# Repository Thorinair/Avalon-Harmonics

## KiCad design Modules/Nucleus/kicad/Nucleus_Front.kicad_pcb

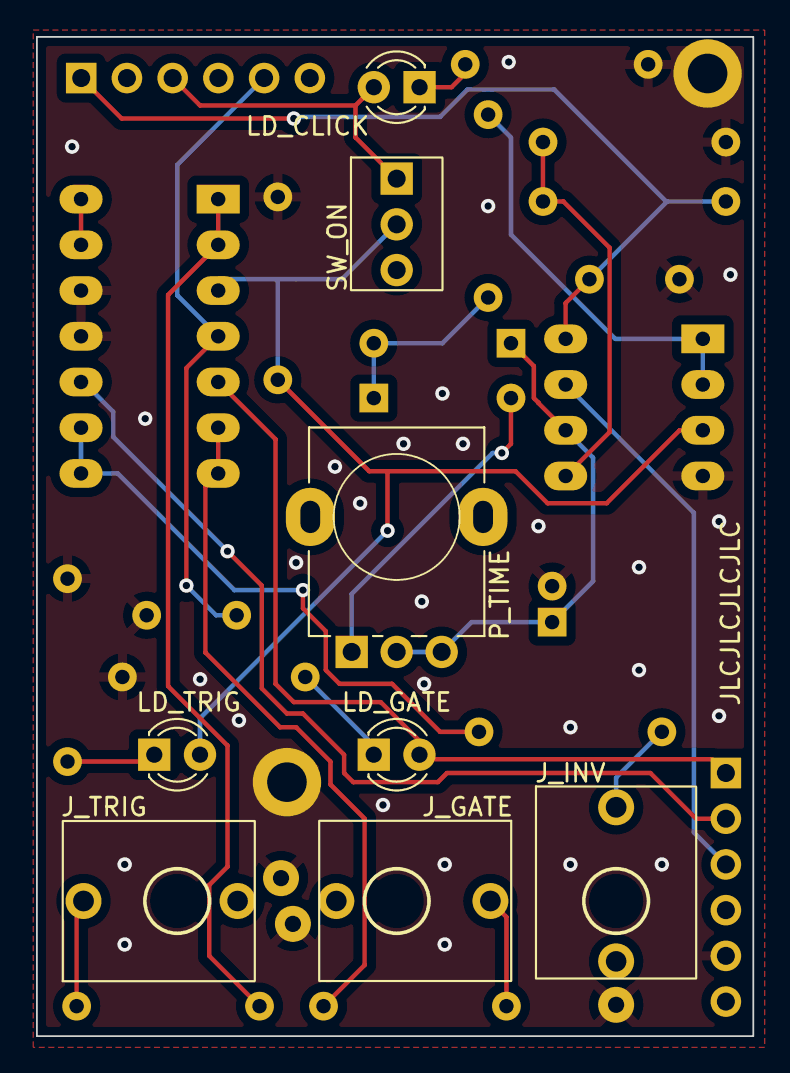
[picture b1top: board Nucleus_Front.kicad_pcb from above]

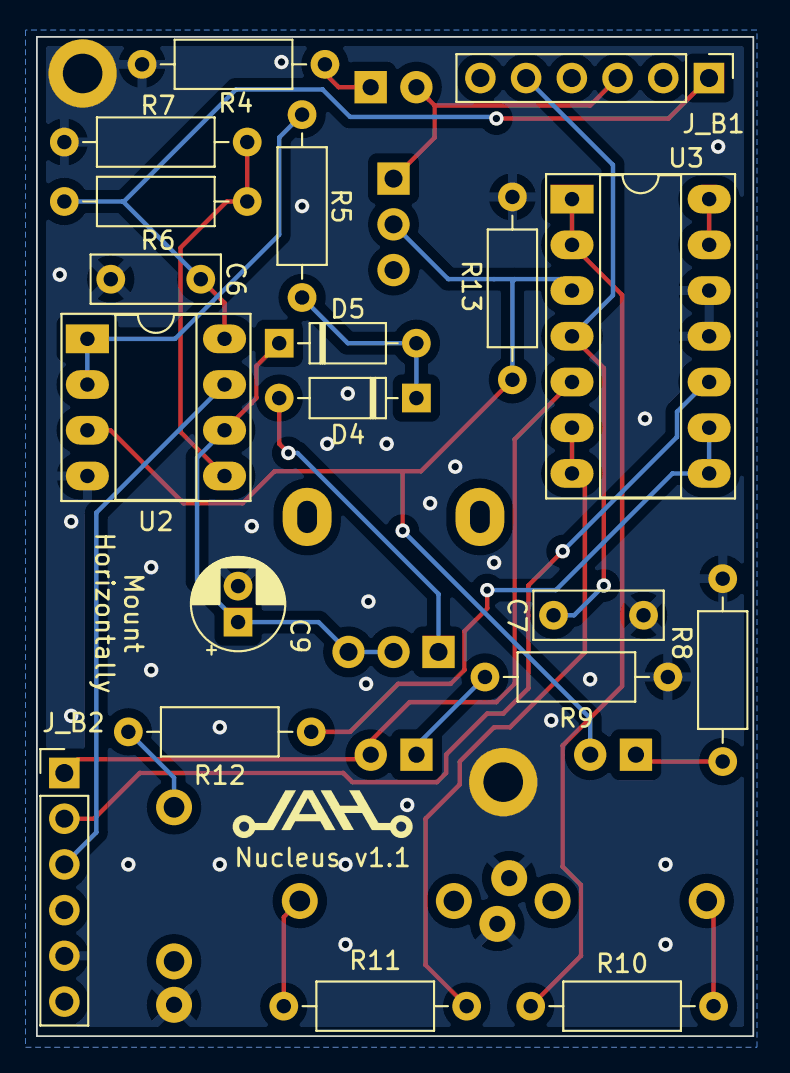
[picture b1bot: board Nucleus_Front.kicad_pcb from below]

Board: 2 copper layers, 39.8 x 55.5 mm, 27 parts (19 on the bottom side), 23 nets.

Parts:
C6, C7: 0.1uF; C_Disc_D7.0mm_W2.5mm_P5.00mm
C9: 10uF; CP_Radial_D5.0mm_P2.00mm
D4, D5: 1N4148; D_DO-35_SOD27_P7.62mm_Horizontal
J_B1, J_B2: Conn_01x06_Female; PinHeader_1x06_P2.54mm_Vertical
J_GATE1: PJ301M-12; PJ301M-12 Offset
J_INV1: PJ301M-12
J_TRIG1: PJ301M-12; PJ301M-12 Offset
LD_CLICK1: LED; LED_D3.0mm_FlatTop
LD_GATE1: LED; LED_D3.0mm_FlatTop
LD_TRIG1: LED; LED_D3.0mm_FlatTop
P_TIME1: B100k; Potentiometer Alpha RD901F-40-00D
R4, R7, R8, R9: 10k; R_Axial_DIN0207_L6.3mm_D2.5mm_P10.16mm_Horizontal
R5: 220; R_Axial_DIN0207_L6.3mm_D2.5mm_P10.16mm_Horizontal
R6: 120k; R_Axial_DIN0207_L6.3mm_D2.5mm_P10.16mm_Horizontal
R10, R11, R12: 1k; R_Axial_DIN0207_L6.3mm_D2.5mm_P10.16mm_Horizontal
R13: 1M; R_Axial_DIN0207_L6.3mm_D2.5mm_P10.16mm_Horizontal
SW_ON1: SW_SPDT; SPDT
U2: LM358; DIP-8_W7.62mm_Socket_LongPads
U3: LM324; DIP-14_W7.62mm_Socket_LongPads

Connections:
+5V: C6.1, J_B1.1, R6.1, U2.8 (V+)
+12V: C7.1, J_B1.5, U3.4 (V+)
/GATE: J_B2.1, LD_GATE1.2 (A), U3.5 (+)
/INV: J_B2.2, U3.10 (+)
/TRIG: LD_TRIG1.2 (A), R13.1, SW_ON1.2 (B), U2.3 (+), U3.3 (+)
GND: C6.2, C7.2, C9.2, J_B2.5, J_GATE1.GND, J_INV1.GND, J_TRIG1.GND, R4.2, R7.2, R8.2, R9.2, R13.2, U2.4 (V-), U3.11 (V-), U3.12 (+)
unnamed: C9.1, D5.1 (K), P_TIME1.2, P_TIME1.3, U2.6 (-)
unnamed: D4.1 (K), D5.2 (A), R5.2
unnamed: D4.2 (A), P_TIME1.1
unnamed: J_B1.3, LD_CLICK1.2 (A), SW_ON1.1 (A)
unnamed: J_B2.3, U2.7
unnamed: J_GATE1.SIG, R11.2
unnamed: J_INV1.SIG, R12.2
unnamed: J_TRIG1.SIG, R10.2
unnamed: LD_CLICK1.1 (K), R4.1
unnamed: LD_GATE1.1 (K), R9.1
unnamed: LD_TRIG1.1 (K), R8.1
unnamed: R5.1, U2.1, U2.2 (-)
unnamed: R6.2, R7.1, U2.5 (+)
unnamed: R10.1, U3.1, U3.2 (-)
unnamed: R11.1, U3.6 (-), U3.7
unnamed: R12.1, U3.8, U3.9 (-)
unnamed: U3.13 (-), U3.14

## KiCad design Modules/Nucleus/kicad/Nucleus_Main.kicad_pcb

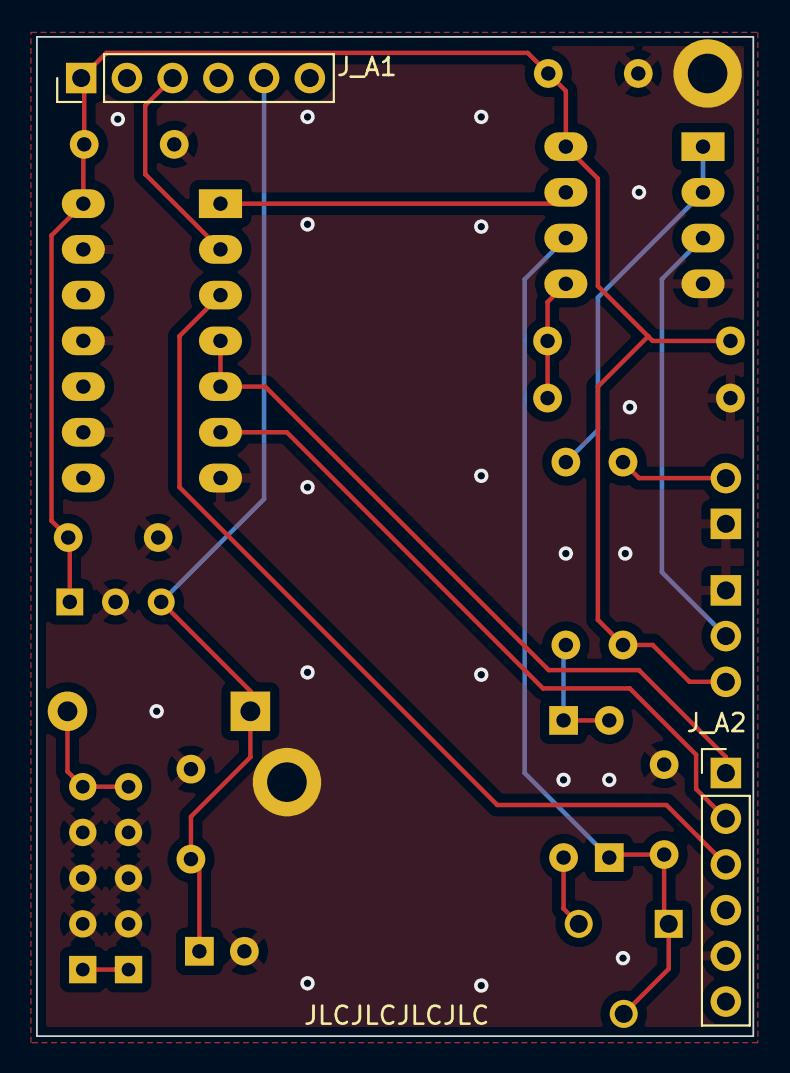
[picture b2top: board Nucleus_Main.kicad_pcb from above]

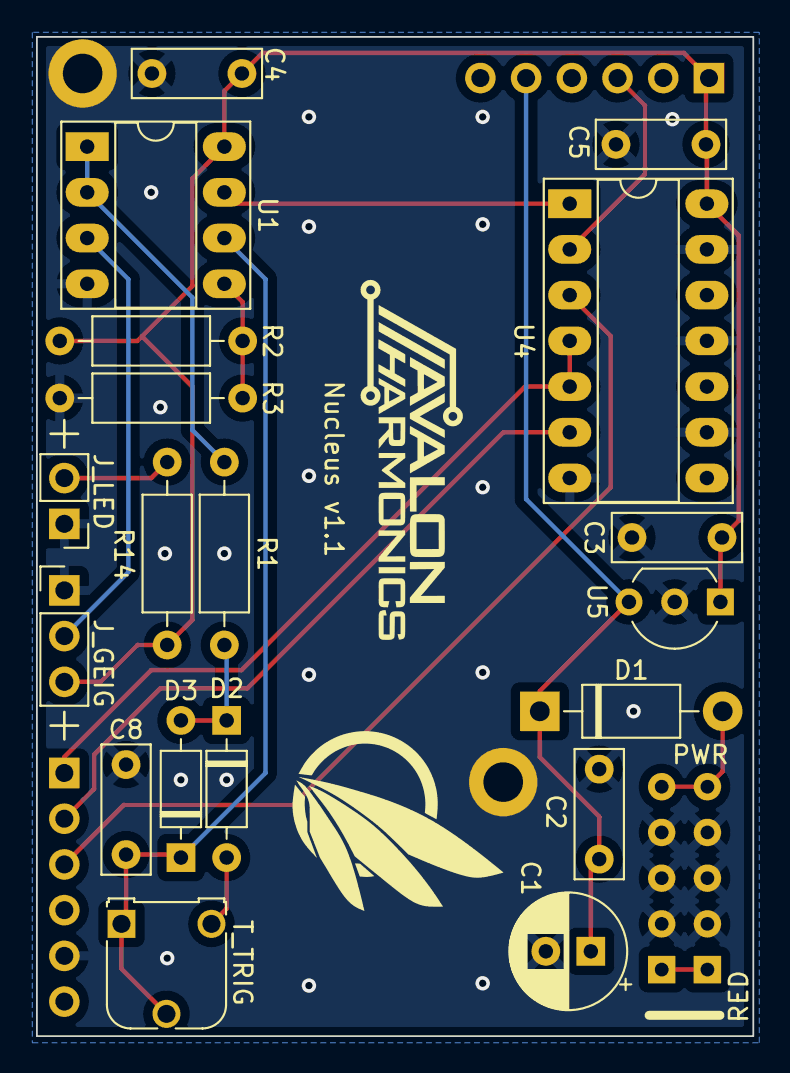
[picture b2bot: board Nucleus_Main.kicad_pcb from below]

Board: 2 copper layers, 39.8 x 55.5 mm, 22 parts (20 on the bottom side), 16 nets.

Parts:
C1: 47uF; CP_Radial_D6.3mm_P2.50mm
C2, C3, C4, C5: 0.1uF; C_Disc_D7.0mm_W2.5mm_P5.00mm
C8: 10nF; C_Disc_D7.0mm_W2.5mm_P5.00mm
D1: 1N4001; D_DO-41_SOD81_P10.16mm_Horizontal
D2, D3: 1N4148; D_DO-35_SOD27_P7.62mm_Horizontal
J_A1, J_A2: Conn_01x06_Male; PinHeader_1x06_P2.54mm_Vertical
J_GEIG1: Conn_01x03_Male; PinHeader_1x03_P2.54mm_Vertical
J_LED1: Conn_01x02_Male; PinHeader_1x02_P2.54mm_Vertical
PWR1: PWR_10_Pin; Eurorack Power 10 Pin
R1: 10; R_Axial_DIN0207_L6.3mm_D2.5mm_P10.16mm_Horizontal
R2: 120k; R_Axial_DIN0207_L6.3mm_D2.5mm_P10.16mm_Horizontal
R3: 10k; R_Axial_DIN0207_L6.3mm_D2.5mm_P10.16mm_Horizontal
R14: 1k; R_Axial_DIN0207_L6.3mm_D2.5mm_P10.16mm_Horizontal
T_TRIG1: B1M; Potentiometer_Runtron_RM-065_Vertical
U1: LM358; DIP-8_W7.62mm_Socket_LongPads
U4: 74HC04; DIP-14_W7.62mm_Socket_LongPads
U5: 78L05; TO-92_Inline_Wide

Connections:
+5V: C3.1, C4.1, C5.1, J_A1.1, J_GEIG1.3, R2.1, R14.2, U1.8 (V+), U4.14 (VCC), U5.1 (VO)
+12V: C1.1, C2.1, D1.1 (K), J_A1.5, U5.3 (VI)
GND: C1.2, C2.2, C3.2, C4.2, C5.2, C8.2, J_A2.5, J_GEIG1.1, J_LED1.1, PWR1.2 (GND), R3.2, U1.4 (V-), U4.7 (GND), U4.9, U4.11, U4.13, U5.2 (GND)
unnamed: C8.1, D3.1 (K), T_TRIG1.1, T_TRIG1.2, U1.6 (-)
unnamed: D1.2 (A), PWR1.1 (+12V)
unnamed: D2.1 (K), D3.2 (A), R1.2
unnamed: D2.2 (A), T_TRIG1.3
unnamed: J_A1.3, U4.2
unnamed: J_A2.1, U4.4, U4.5
unnamed: J_A2.2, U4.6
unnamed: J_A2.3, U4.3
unnamed: J_GEIG1.2, U1.3 (+)
unnamed: J_LED1.2, R14.1
unnamed: R1.1, U1.1, U1.2 (-)
unnamed: R2.2, R3.1, U1.5 (+)
unnamed: U1.7, U4.1

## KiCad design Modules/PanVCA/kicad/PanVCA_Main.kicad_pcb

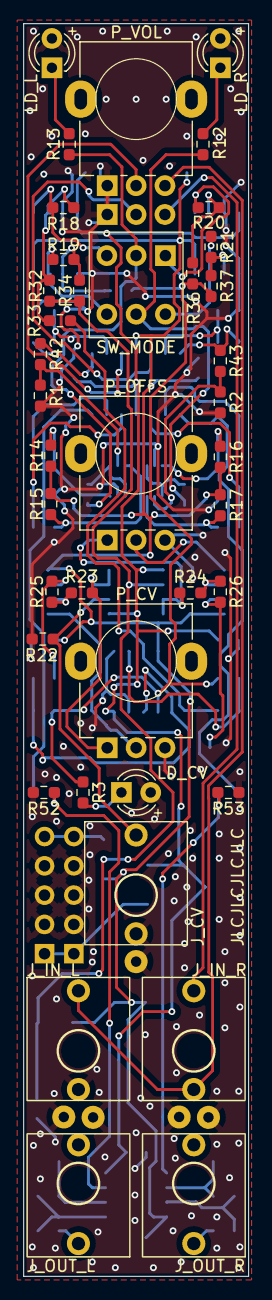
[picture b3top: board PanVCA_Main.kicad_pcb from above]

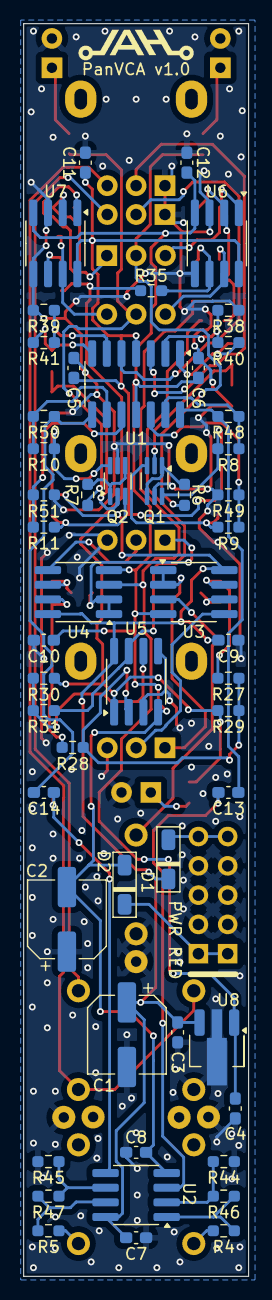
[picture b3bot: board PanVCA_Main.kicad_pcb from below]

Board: 2 copper layers, 19.5 x 108.6 mm, 92 parts (53 on the bottom side), 62 nets.

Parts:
C1, C2: 47uF; CP_Elec_6.3x5.3
C3, C4, C5, C6, C7, C8, C9, C10, C11, C12, C13, C14: 0.1uF; C_0603_1608Metric_Pad1.08x0.95mm_HandSolder
D1, D2: FM4001; D_SOD-123F_AH
J_CV: PJ301M-12
J_IN_L: PJ301M-12; PJ301M-12 Offset
J_IN_R: PJ301M-12; PJ301M-12 Offset
J_OUT_L: PJ301M-12; PJ301M-12 Offset
J_OUT_R: PJ301M-12; PJ301M-12 Offset
LD_CV: LED (Bi); LED_D3.0mm_FlatTop
LD_L: LED; LED_D3.0mm_FlatTop
LD_R: LED; LED_D3.0mm_FlatTop
PWR1: PWR_10_Pin; Eurorack Power 10 Pin
P_CV: B50k; Potentiometer Alpha RD901F-40-00D
P_OFFS: B50k; Potentiometer Alpha RD901F-40-00D
P_VOL: A100k; Potentiometer Alpha Dual RD901F-40-00D
Q1, Q2: BCM847BS; SOT-363_SC-70-6_Handsoldering
R1, R2: 100; R_0603_1608Metric_Pad0.98x0.95mm_HandSolder
R3, R4, R5: 1k; R_0603_1608Metric_Pad0.98x0.95mm_HandSolder
R6, R7: 10k; R_0603_1608Metric_Pad0.98x0.95mm_HandSolder
R8, R9, R10, R11: 10k 0.1%; R_0603_1608Metric_Pad0.98x0.95mm_HandSolder
R12, R13: 16k; R_0603_1608Metric_Pad0.98x0.95mm_HandSolder
R14, R15, R16, R17: 20k 0.1%; R_0603_1608Metric_Pad0.98x0.95mm_HandSolder
R18, R19, R20, R21: 82k; R_0603_1608Metric_Pad0.98x0.95mm_HandSolder
R22, R23, R24, R25, R26, R27, R28, R29, R30, R31, R32, R33, R34, R35, R36, R37, R38, R39, R40, R41, R42, R43, R44, R45, R46, R47: 100k; R_0603_1608Metric_Pad0.98x0.95mm_HandSolder
R48, R49, R50, R51: 100k 0.1%; R_0603_1608Metric_Pad0.98x0.95mm_HandSolder
R52, R53: 240k; R_0603_1608Metric_Pad0.98x0.95mm_HandSolder
SW_MODE: SW_DPDT_x2; DPDT
U1: TL074; SO-14_3.9x8.65mm_P1.27mm_AH
U2, U3, U4, U5, U6, U7: TL072; SO-8_3.9x4.9mm_P1.27mm_AH
U8: 78L05; SOT-89-3_Handsoldering

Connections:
+5V: C4.1, R32.2, R34.2, U4.3 (+), U8.1 (VO)
+12V: C1.1, C3.1, C5.1, C7.1, C9.1, C11.1, D1.1 (K), R14.1, R15.1, R16.1, R17.1, U1.4 (V+), U2.8 (V+), U3.8 (V+), U4.8 (V+), U5.8 (V+), U6.8 (V+), U7.8 (V+), U8.3 (VI)
-12V: C2.2, C6.2, C8.2, C10.2, C12.2, D2.2 (A), U1.11 (V-), U2.4 (V-), U3.4 (V-), U4.4 (V-), U5.4 (V-), U6.4 (V-), U7.4 (V-)
/CTRL_L: R6.1, R13.1, SW_MODE.2 (B)
/CTRL_R: R7.1, R12.1, SW_MODE.5 (B)
/CV_MIX: R3.2, R29.1, R30.1, R35.2, R36.2, R37.2, U5.1
/CV_PAN_L: R18.2, SW_MODE.3 (C), U6.1
/CV_PAN_R: R19.1, SW_MODE.6 (C), U6.7
/CV_VCA_L: R20.2, SW_MODE.1 (A), U7.1
/CV_VCA_R: R21.1, SW_MODE.4 (A), U7.7
/INF_L: J_IN_L.SIG, J_IN_R.SW, P_VOL.3
/INF_R: J_IN_R.SIG, P_VOL.6
/IN_CV: J_CV.SIG, R22.2, U3.3 (+)
/IN_L: P_VOL.2, U1.3 (+)
/IN_R: P_VOL.5, U1.5 (+)
/OUT_L: J_OUT_L.SIG, R4.2
/OUT_R: J_OUT_R.SIG, R5.2
/PRE_L: C13.2, R48.1, U1.14
/PRE_R: C14.2, R50.1, U1.8
GND: C1.2, C2.1, C3.2, C4.2, C5.2, C6.1, C7.2, C8.1, C9.2, C10.1, C11.2, C12.1, J_CV.GND, J_CV.SW, J_IN_L.GND, J_IN_L.SW, J_IN_R.GND, J_OUT_L.GND, J_OUT_R.GND, LD_CV.2 (A), LD_L.2 (A), LD_R.2 (A), PWR1.2 (GND), P_CV.3, P_OFFS.3, P_VOL.1, P_VOL.4, Q1.5 (B2), Q2.5 (B2), R1.2, R2.2, R22.1, R38.2, R39.2, R44.2, R45.2, R49.1, R51.1, R52.1, R53.1, U5.3 (+), U5.5 (+), U6.3 (+), U6.5 (+), U7.3 (+), U7.5 (+), U8.2 (GND)
unnamed: D1.2 (A), PWR1.1 (+12V)
unnamed: D2.1 (K), PWR1.3 (-12V)
unnamed: LD_CV.1 (K), R3.1
unnamed: LD_L.1 (K), R13.2
unnamed: LD_R.1 (K), R12.2
unnamed: Q1.2 (B1), R1.1, R42.2
unnamed: Q1.6 (C1), R8.2, R14.2
unnamed: Q1.1 (E1), Q1.4 (E2), R6.2
unnamed: Q1.3 (C2), R9.2, R15.2
unnamed: Q2.2 (B1), R2.1, R43.2
unnamed: Q2.6 (C1), R10.2, R16.2
unnamed: Q2.1 (E1), Q2.4 (E2), R7.2
unnamed: Q2.3 (C2), R11.2, R17.2
unnamed: R4.1, R46.1, U2.1
unnamed: R25.1, R27.2, U3.7
unnamed: R26.1, R28.2, U4.7
unnamed: R31.1, R33.2, U5.7
unnamed: R40.1, R42.1, U1.1
unnamed: R41.1, R43.1, U1.7
unnamed: R5.1, R47.1, U2.7
unnamed: R38.1, R40.2, U1.2 (-)
unnamed: R39.1, R41.2, U1.6 (-)
unnamed: R11.1, R51.2, U1.10 (+)
unnamed: R10.1, R50.2, U1.9 (-)
unnamed: R9.1, R49.2, U1.12 (+)
unnamed: R8.1, R48.2, U1.13 (-)
unnamed: C13.1, R52.2, U2.3 (+)
unnamed: R44.1, R46.2, U2.2 (-)
unnamed: C14.1, R53.2, U2.5 (+)
unnamed: R45.1, R47.2, U2.6 (-)
unnamed: P_CV.1, R23.2, U3.1, U3.2 (-)
unnamed: P_CV.2, U3.5 (+)
unnamed: R23.1, R25.2, U3.6 (-)
unnamed: P_OFFS.1, R24.2, U4.1, U4.2 (-)
unnamed: P_OFFS.2, U4.5 (+)
unnamed: R24.1, R26.2, U4.6 (-)
unnamed: R27.1, R28.1, R29.2, U5.2 (-)
unnamed: R30.2, R31.2, U5.6 (-)
unnamed: R18.1, R32.1, R33.1, U6.2 (-)
unnamed: R19.2, R34.1, R35.1, U6.6 (-)
unnamed: R20.1, R36.1, U7.2 (-)
unnamed: R21.2, R37.1, U7.6 (-)

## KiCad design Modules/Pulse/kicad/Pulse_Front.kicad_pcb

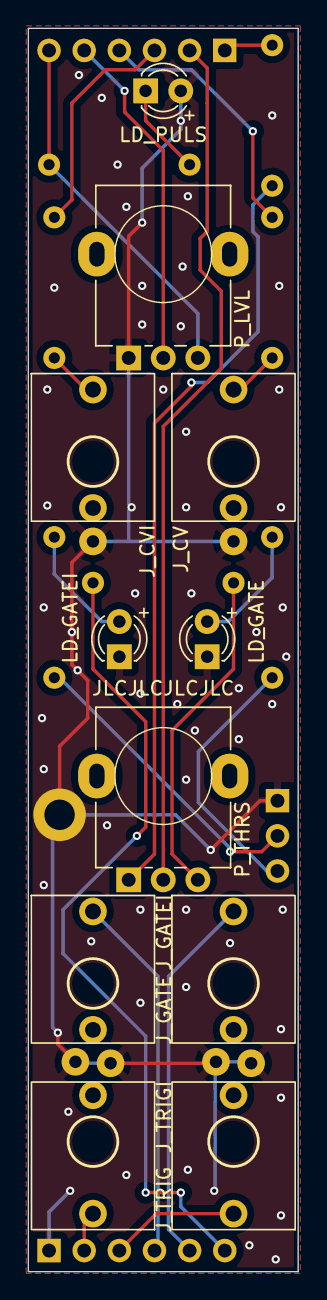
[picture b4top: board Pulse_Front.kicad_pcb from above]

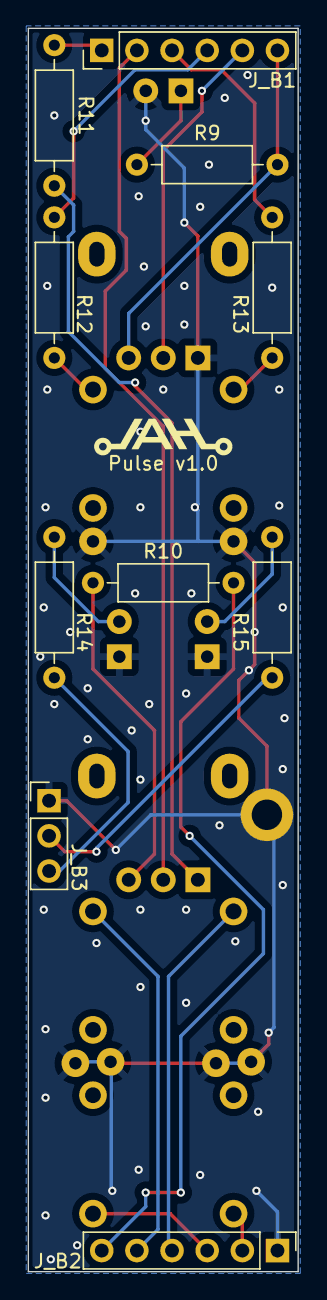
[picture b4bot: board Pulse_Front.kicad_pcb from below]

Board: 2 copper layers, 19.5 x 89.9 mm, 21 parts (10 on the bottom side), 21 nets.

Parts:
J_B1, J_B2: Conn_01x06_Female; PinHeader_1x06_P2.54mm_Vertical
J_B3: Conn_01x03_Female; PinHeader_1x03_P2.54mm_Vertical
J_CV: PJ301M-12
J_CVI: PJ301M-12
J_GATE: PJ301M-12; PJ301M-12 Offset
J_GATEI: PJ301M-12; PJ301M-12 Offset
J_TRIG: PJ301M-12; PJ301M-12 Offset
J_TRIGI: PJ301M-12; PJ301M-12 Offset
LD_GATE: LED; LED_D3.0mm_FlatTop
LD_GATEI: LED; LED_D3.0mm_FlatTop
LD_PULS: LED (Bi); LED_D3.0mm_FlatTop
P_LVL: B100k; Potentiometer Alpha RD901F-40-00D
P_THRS: B100k; Potentiometer Alpha RD901F-40-00D
R9, R12, R13: 1k; R_Axial_DIN0207_L6.3mm_D2.5mm_P10.16mm_Horizontal
R10, R11: 47k; R_Axial_DIN0207_L6.3mm_D2.5mm_P10.16mm_Horizontal
R14, R15: 10k; R_Axial_DIN0207_L6.3mm_D2.5mm_P10.16mm_Horizontal

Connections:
+12V: J_B2.6, R10.1
-12V: J_B1.1, R11.2
GND: J_B2.1, J_B3.1, J_CV.GND, J_CVI.GND, J_GATE.GND, J_GATEI.GND, J_TRIG.GND, J_TRIGI.GND, LD_GATE.1 (K), LD_GATEI.1 (K), LD_PULS.2 (A), P_LVL.1
unnamed: J_B1.2, P_THRS.2
unnamed: J_B1.3, R13.1
unnamed: J_B1.4, R12.1
unnamed: J_B1.5, P_LVL.2
unnamed: J_B1.6, P_LVL.3, R9.2
unnamed: J_B2.2, J_TRIGI.SIG
unnamed: J_B2.3, J_TRIG.SIG
unnamed: J_B2.4, J_GATEI.SIG
unnamed: J_B2.5, J_GATE.SIG
unnamed: J_B3.2, R15.2
unnamed: J_B3.3, R14.2
unnamed: J_CV.SIG, R12.2
unnamed: J_CVI.SIG, R13.2
unnamed: LD_GATE.2 (A), R14.1
unnamed: LD_GATEI.2 (A), R15.1
unnamed: LD_PULS.1 (K), R9.1
unnamed: P_THRS.1, R11.1
unnamed: P_THRS.3, R10.2

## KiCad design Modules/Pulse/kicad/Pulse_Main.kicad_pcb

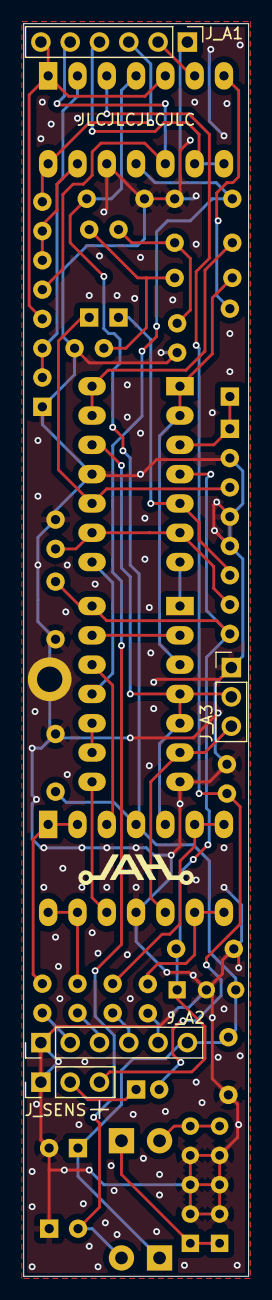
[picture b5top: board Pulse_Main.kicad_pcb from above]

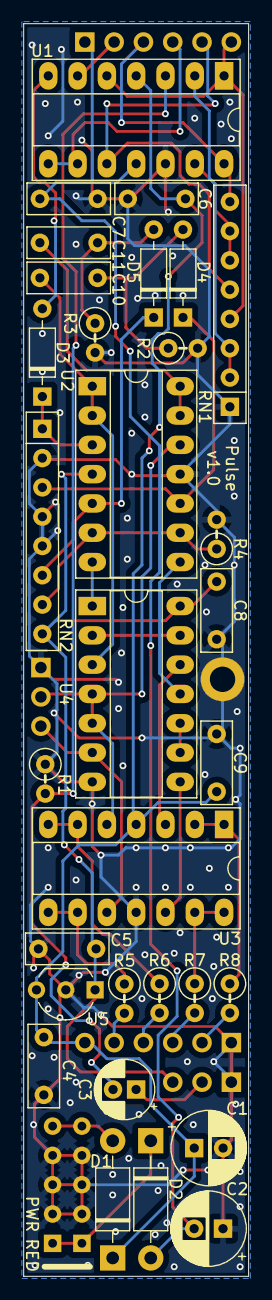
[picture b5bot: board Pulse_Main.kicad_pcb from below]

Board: 2 copper layers, 19.5 x 108.6 mm, 36 parts (32 on the bottom side), 40 nets.

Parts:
C1, C2: 47uF; CP_Radial_D6.3mm_P2.50mm
C3: 10uF; CP_Radial_D5.0mm_P2.00mm
C4, C5, C6, C7, C8, C9, C10, C11: 0.1uF; C_Disc_D7.0mm_W2.5mm_P5.00mm
D1, D2: 1N4001; D_DO-41_SOD81_P10.16mm_Horizontal
D3, D4, D5: 1N4148; D_DO-35_SOD27_P7.62mm_Horizontal
J_A1, J_A2: Conn_01x06_Male; PinHeader_1x06_P2.54mm_Vertical
J_A3: Conn_01x03_Male; PinHeader_1x03_P2.54mm_Vertical
J_SENS: Conn_01x03_Male; PinHeader_1x03_P2.54mm_Vertical
PWR1: PWR_10_Pin; Eurorack Power 10 Pin
R1: 120k; R_Axial_DIN0207_L6.3mm_D2.5mm_P2.54mm_Vertical
R2, R3: 47k; R_Axial_DIN0207_L6.3mm_D2.5mm_P2.54mm_Vertical
R4: 10k; R_Axial_DIN0207_L6.3mm_D2.5mm_P2.54mm_Vertical
R5, R6, R7, R8: 1k; R_Axial_DIN0207_L6.3mm_D2.5mm_P2.54mm_Vertical
RN1, RN2: 100k; R_Array_SIP8
U1: TL074; DIP-14_W7.62mm_Socket_LongPads
U2, U3: LM324; DIP-14_W7.62mm_Socket_LongPads
U4: 74HC04; DIP-14_W7.62mm_Socket_LongPads
U5: 78L05; TO-92_Inline_Wide

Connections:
+5V: C5.1, C8.1, J_SENS.3, RN2.8 (R4.2), U2.4 (V+), U4.14 (VCC), U5.1 (VO)
+12V: C1.1, C4.1, C6.1, C9.1, D1.1 (K), J_A2.6, U1.4 (V+), U3.4 (V+), U5.3 (VI)
-12V: C2.2, C7.2, D2.2 (A), J_A1.1, U1.11 (V-)
/DIV: R4.1, RN2.7 (R4.1), U2.6 (-), U2.9 (-)
/GATE: C10.1, U2.1, U2.2 (-), U4.3
/GATEI: J_A3.2, U2.12 (+), U3.5 (+), U4.4, U4.5
/OUT_CV: J_A1.4, U1.8, U1.9 (-)
/OUT_CVI: J_A1.3, RN1.8 (R4.2), U1.14
/RET: J_A1.5, RN1.5 (R3.1), U1.10 (+)
/SIG: J_A1.6, RN1.4 (R2.2), U1.1, U1.5 (+)
/THRS: J_A1.2, U1.6 (-)
/TRIG: U2.8, U4.11
/TRIGI: U2.7, U4.1
GND: C1.2, C2.1, C4.2, C5.2, C6.2, C7.1, C8.2, C9.2, J_A2.1, J_A3.1, J_SENS.1, PWR1.2 (GND), R1.1, R2.2, R3.2, R4.2, RN1.1 (R1.1), RN2.2 (R1.2), RN2.4 (R2.2), RN2.5 (R3.1), U1.12 (+), U2.11 (V-), U3.11 (V-), U4.7 (GND), U5.2 (GND)
unnamed: D1.2 (A), PWR1.1 (+12V)
unnamed: D2.1 (K), PWR1.3 (-12V)
unnamed: D3.2 (A), U1.7
unnamed: D3.1 (K), RN2.1 (R1.1), U2.3 (+)
unnamed: C10.2, D4.2 (A), R2.1
unnamed: D4.1 (K), RN2.3 (R2.1), U2.10 (+)
unnamed: C11.2, D5.2 (A), R3.1
unnamed: D5.1 (K), RN2.6 (R3.2), U2.5 (+)
unnamed: J_A2.2, R8.2
unnamed: J_A2.3, R7.2
unnamed: J_A2.4, R6.2
unnamed: J_A2.5, R5.2
unnamed: J_A3.3, U3.10 (+), U4.6
unnamed: C3.1, J_SENS.2
unnamed: RN1.2 (R1.2), RN1.3 (R2.1), U1.2 (-)
unnamed: RN1.6 (R3.2), RN1.7 (R4.1), U1.13 (-)
unnamed: C3.2, R1.2, U1.3 (+)
unnamed: C11.1, U2.13 (-), U2.14
unnamed: U3.3 (+), U4.12
unnamed: R8.1, U3.1, U3.2 (-)
unnamed: R6.1, U3.6 (-), U3.7
unnamed: R5.1, U3.8, U3.9 (-)
unnamed: U3.12 (+), U4.8
unnamed: R7.1, U3.13 (-), U3.14
unnamed: U4.9, U4.10
unnamed: U4.2, U4.13
